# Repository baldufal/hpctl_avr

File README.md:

# HPCTL AVR
Software for Atmega48/88/168/328 controller of HPCTL heating and ventilation controller project.

We use it with Microchip Studio and Atmega168.

# Task
This mc is controlled by a [ESP32](https://github.com/baldufal/hpctl_arduino/tree/main) via I2C bus.
It drives 8 solid state relais (SSRs) and 8 mechanical relais and reports the state of 4 universal binary inputs.
3 of the SSRs are connected to a heater. They are driven with very slow PWM with a period of 10s.
The mechanical relais control one ventilator.
Another ventilator is controlled via PWM on one of the SSR outputs (SSR3/PD3).

# I2C Interface
The I2C interface exposes 6 8bit registers:
Register | Semantics | Allowed values (writing)
---|---|---
0 | Heater level | 0-30
1 | Vent IN | 0-255
2 | Vent OUT | 0-6
3 | SSRs | 0b000x0xxx
4 | Checksum | -
5 | Inputs | -

- The three most significant bits of register 3 are determined by heater level. They cannot be set manually, but their current values can be read from this register.
- Similarly for 4th bit (0b00001000) is controlled by the Vent OUT level (1kHz PWM).
- The checksum is the inverse of the 8bit sum of registers 0 to 3.
- The lower 4 bits of register 5 contain the actual input states.
- The upper 4 bits of register 5 contain the bitwise inverse of the input states.

# Board
We use the controller on a custom PCB. It additionally provides the corresponding ESP32 with 5V supply voltage and a debounced terminal for 4 buttons which are connected directly to the ESP32.

The layout file uses a wrong footprint for the mC.

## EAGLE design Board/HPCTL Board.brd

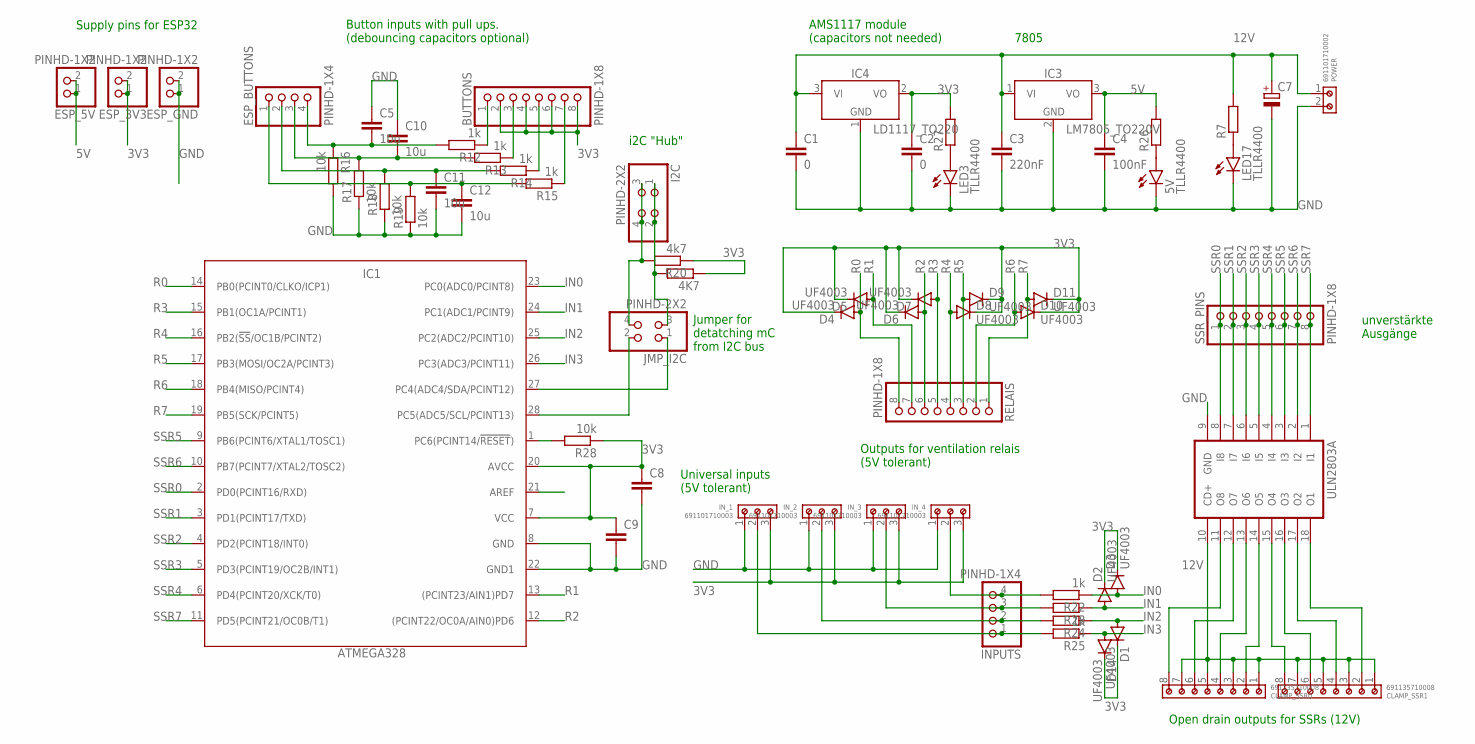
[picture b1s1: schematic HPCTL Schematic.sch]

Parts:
4K7: R-EU_0207/10; 0207/10
5V: TLLR4400; LED3MM
BUTTONS: PINHD-1X8; 1X08
C1, C2: 0; C0805K
C3: 220nF; C0805K
C4: 100nF; C0805K
C5, C10, C11, C12: 10u; C0805K
C7: CPOL-EUE2-5; E2-5
C8, C9: C-EUC0805K; C0805K
CLAMP_SSR0, CLAMP_SSR1: 691135710008
D1, D2, D3, D4, D5, D6, D7, D8, D9, D10, D11, D14: UF4003; DO41-10
ESP_3V3, ESP_5V: PINHD-1X2; 1X02
ESP_BUTTONS: PINHD-1X4; 1X04
ESP_GND: PINHD-1X2; 1X02
I2C: PINHD-2X2; 2X02
IC1: ATMEGA328; DIP1016W53P254L3467H457Q28B
IC3: LM7805_TO220V; TO220V
IC4: LD1117_TO220; TO220V
INPUTS: PINHD-1X4; 1X04
IN_1, IN_2, IN_3, IN_4: 691101710003
JMP_I2C: PINHD-2X2; 2X02
LED3, LED17: TLLR4400; LED3MM
POWER: 691101710002
R7, R23, R24, R26, R27: R-EU_0207/10; 0207/10
R12, R13, R14, R15, R22, R25: 1k; 0207/10
R16, R17, R18, R19, R28: 10k; 0207/10
R20: 4k7; 0207/10
RELAIS: PINHD-1X8; 1X08
SSR_PINS: PINHD-1X8; 1X08
ULN2803A: ULN2804A; DIL18

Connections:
3V3: 4K7.1, BUTTONS.2, BUTTONS.4, BUTTONS.6, BUTTONS.8, C2.1, C8.1, C9.1, D1.C, D2.C, D3.C, D4.C, D5.C, D6.C, D7.C, D8.C, D9.C, D10.C, D11.C, D14.C, ESP_3V3.1, ESP_3V3.2, IC1.7 (VCC), IC1.20 (AVCC), IC4.2 (VO), IN_1.3, IN_2.3, IN_3.3, IN_4.3, R20.1, R27.2, R28.1
5V: C4.1, ESP_5V.1, ESP_5V.2, IC3.3 (VO), R26.2
12V: C1.1, C3.1, C7.+, CLAMP_SSR0.1, CLAMP_SSR0.3, CLAMP_SSR0.5, CLAMP_SSR0.7, CLAMP_SSR1.1, CLAMP_SSR1.3, CLAMP_SSR1.5, CLAMP_SSR1.7, IC3.1 (VI), IC4.3 (VI), POWER.1, R7.2, ULN2803A.10 (CD+)
GND: 5V.K (C), C1.2, C2.2, C3.2, C4.2, C5.1, C7.-, C8.2, C9.2, C10.1, C11.2, C12.2, ESP_GND.1, ESP_GND.2, IC1.8 (GND), IC1.22 (GND1), IC3.2 (GND), IC4.1 (GND), IN_1.1, IN_2.1, IN_3.1, IN_4.1, LED3.K (C), LED17.K (C), POWER.2, R16.2, R17.1, R18.1, R19.1, ULN2803A.9 (GND)
IN0: D3.A, IC1.23 (PC0(ADC0/PCINT8)), R22.1
IN1: D2.A, IC1.24 (PC1(ADC1/PCINT9)), R23.1
IN2: D1.A, IC1.25 (PC2(ADC2/PCINT10)), R24.1
IN3: D14.A, IC1.26 (PC3(ADC3/PCINT11)), R25.1
unnamed: I2C.3, I2C.4, JMP_I2C.4, R20.2
unnamed: 4K7.2, I2C.1, I2C.2, JMP_I2C.3
unnamed: BUTTONS.7, R15.1
unnamed: BUTTONS.5, R14.1
unnamed: BUTTONS.3, R13.1
unnamed: BUTTONS.1, R12.1
unnamed: LED17.A, R7.1
unnamed: CLAMP_SSR0.8, ULN2803A.11 (O8)
unnamed: CLAMP_SSR0.6, ULN2803A.12 (O7)
unnamed: CLAMP_SSR0.4, ULN2803A.13 (O6)
unnamed: CLAMP_SSR0.2, ULN2803A.14 (O5)
unnamed: CLAMP_SSR1.8, ULN2803A.15 (O4)
unnamed: CLAMP_SSR1.6, ULN2803A.16 (O3)
unnamed: CLAMP_SSR1.4, ULN2803A.17 (O2)
unnamed: CLAMP_SSR1.2, ULN2803A.18 (O1)
unnamed: C5.2, ESP_BUTTONS.4, R12.2, R16.1
unnamed: C12.1, ESP_BUTTONS.1, R15.2, R19.2
unnamed: C11.1, ESP_BUTTONS.2, R14.2, R18.2
unnamed: INPUTS.4, IN_4.2, R22.2
unnamed: C10.2, ESP_BUTTONS.3, R13.2, R17.2
unnamed: INPUTS.3, IN_3.2, R23.2
unnamed: INPUTS.2, IN_2.2, R24.2
unnamed: INPUTS.1, IN_1.2, R25.2
unnamed: 5V.A, R26.1
unnamed: LED3.A, R27.1
unnamed: IC1.1 (PC6(PCINT14/!RESET!)), R28.2
R0: D4.A, IC1.14 (PB0(PCINT0/CLKO/ICP1)), RELAIS.8
R1: D5.A, IC1.13 ((PCINT23/AIN1)PD7), RELAIS.7
R2: D6.A, IC1.12 ((PCINT22/OC0A/AIN0)PD6), RELAIS.6
R3: D7.A, IC1.15 (PB1(OC1A/PCINT1)), RELAIS.5
R4: D8.A, IC1.16 (PB2(!SS!/OC1B/PCINT2)), RELAIS.4
R5: D9.A, IC1.17 (PB3(MOSI/OC2A/PCINT3)), RELAIS.3
R6: D10.A, IC1.18 (PB4(MISO/PCINT4)), RELAIS.2
R7: D11.A, IC1.19 (PB5(SCK/PCINT5)), RELAIS.1
SCL: IC1.28 (PC5(ADC5/SCL/PCINT13)), JMP_I2C.2
SDA: IC1.27 (PC4(ADC4/SDA/PCINT12)), JMP_I2C.1
SSR0: IC1.2 (PD0(PCINT16/RXD)), SSR_PINS.1, ULN2803A.8 (I8)
SSR1: IC1.3 (PD1(PCINT17/TXD)), SSR_PINS.2, ULN2803A.7 (I7)
SSR2: IC1.4 (PD2(PCINT18/INT0)), SSR_PINS.3, ULN2803A.6 (I6)
SSR3: IC1.5 (PD3(PCINT19/OC2B/INT1)), SSR_PINS.4, ULN2803A.5 (I5)
SSR4: IC1.6 (PD4(PCINT20/XCK/T0)), SSR_PINS.5, ULN2803A.4 (I4)
SSR5: IC1.9 (PB6(PCINT6/XTAL1/TOSC1)), SSR_PINS.6, ULN2803A.3 (I3)
SSR6: IC1.10 (PB7(PCINT7/XTAL2/TOSC2)), SSR_PINS.7, ULN2803A.2 (I2)
SSR7: IC1.11 (PD5(PCINT21/OC0B/T1)), SSR_PINS.8, ULN2803A.1 (I1)

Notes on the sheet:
Button inputs with pull ups. (debouncing capacitors optional)
7805
AMS1117 module (capacitors not needed)
Supply pins for ESP32
Jumper for detatching mC from I2C bus
i2C "Hub"
unverstärkte Ausgänge
Open drain outputs for SSRs (12V)
Outputs for ventilation relais (5V tolerant)
Universal inputs (5V tolerant)

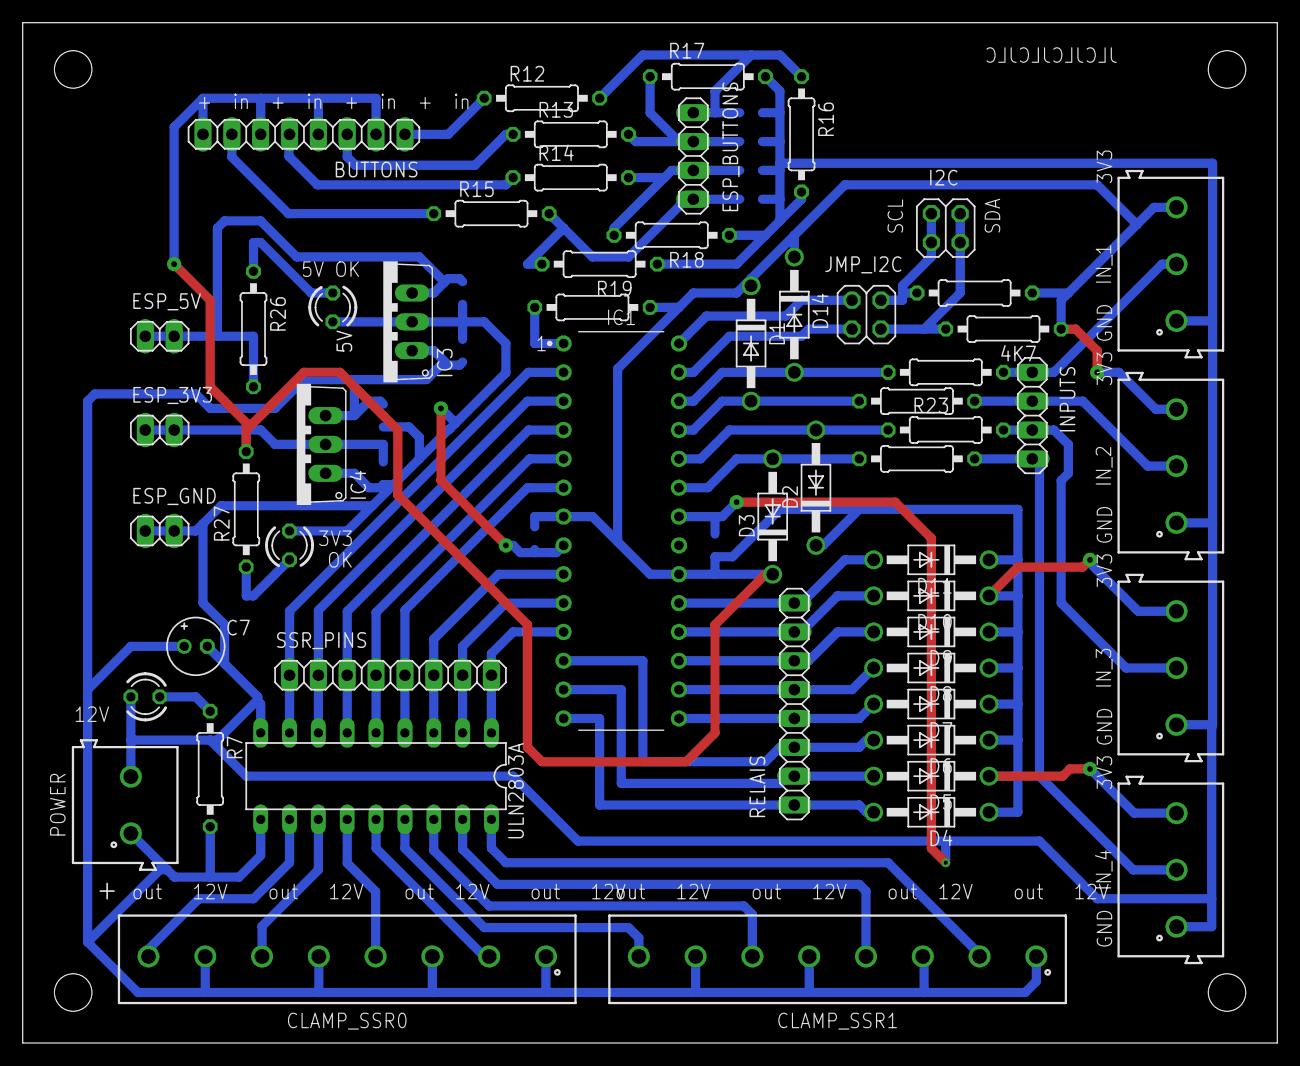
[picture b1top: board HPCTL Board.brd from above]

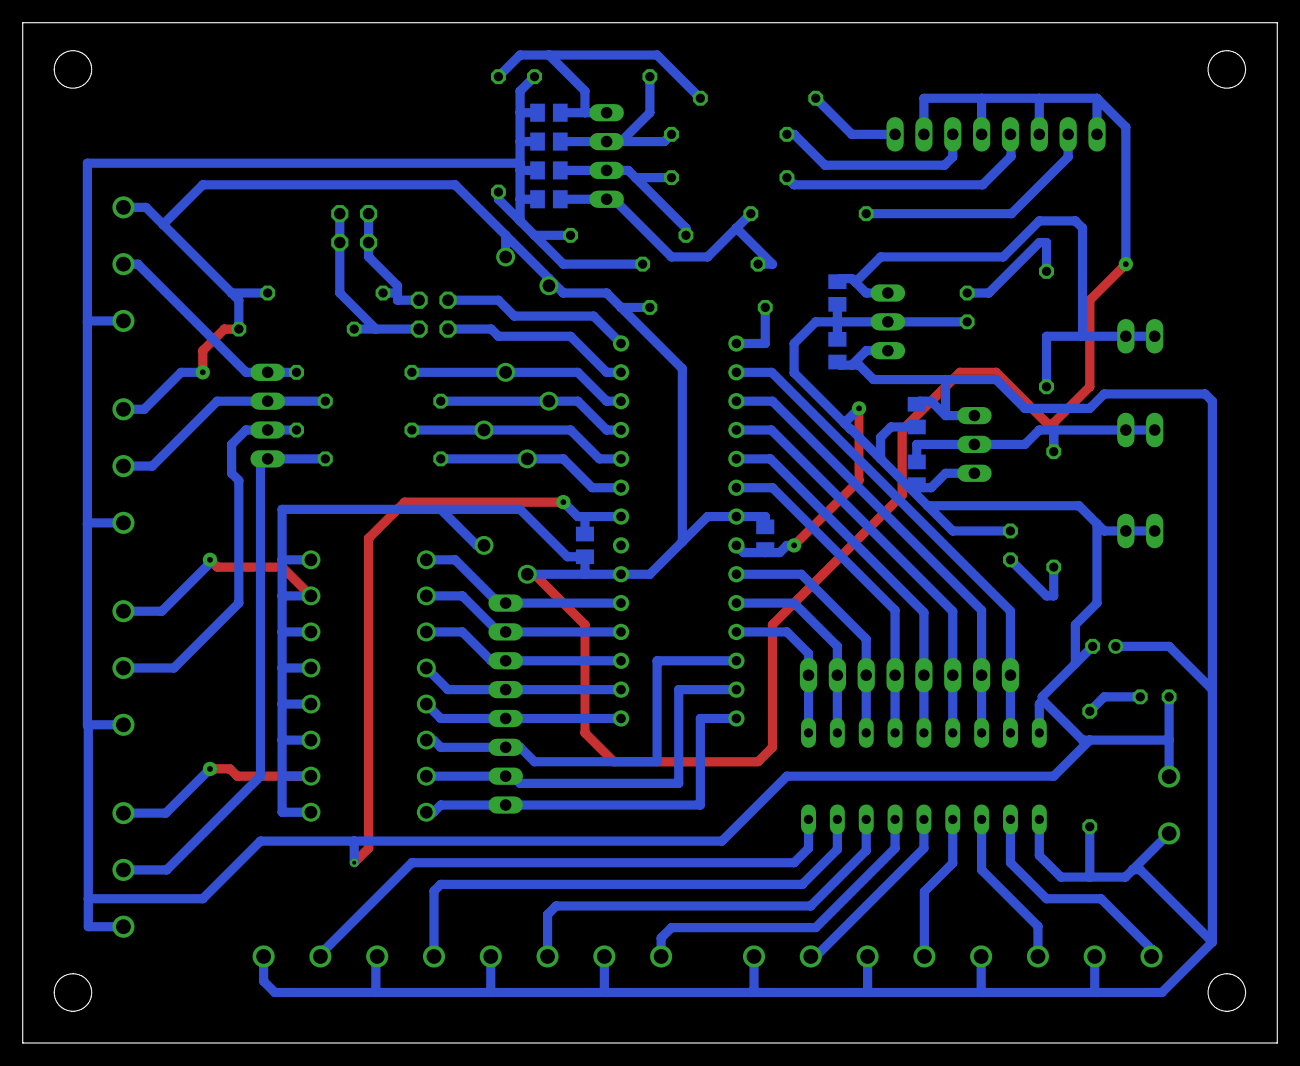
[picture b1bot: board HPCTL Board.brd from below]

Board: 2 copper layers, 110.5 x 89.8 mm, 65 parts (10 on the bottom side), 52 nets.

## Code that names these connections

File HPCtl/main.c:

/*
* HPCtl.c
*
* Created: 05.10.2023 19:40:37
* For Atmega168
* Author : falkb
*/

#ifndef F_CPU
# define F_CPU 8000000UL
#endif

#include <avr/io.h>
#include <avr/interrupt.h>
#include <avr/wdt.h>
#include <util/delay.h>
#include "twislave.h"
#include "relay.h"

#define PWM_TICK_FREQUENCY_HZ 1
#define PWM_PERIOD_SECONDS 10
// The number of heater levels, defined by the PWM cycle.
#define NUM_HEATER_LEVELS (PWM_TICK_FREQUENCY_HZ * PWM_PERIOD_SECONDS * 3 + 1)

// A tick-counter driven by a timer.
// This counts seconds modulo some number.
volatile uint8_t timer_ticks;

// Initializes outputs.
static void io_init() {
	// No pull ups necessary because of external pull ups.
	// We use pull ups anyway to make debugging without external pull ups easier.
	
	// Outputs:
	// PD0..PD2, PD4:		General purpose SSRs
	// PD3:					Ventilation PWM
	// PD5, PB6, PB7:		Heater SSRs
	// PD6, PD7, PB0..PB5:	Relais
	
	// Inputs:
	// PC0..PC3:			General purpose Inputs
	// PC4, PC5:			I2C
	
	// Vent pins high = vent off
	PORTB = 0b00111111;
	DDRB = 0xFF;
	
	// PC0 to PC5 as inputs with pull ups enabled
	PORTC = 0xFF;
	DDRC = 0x00;
	
	// Vent pins high = vent off
	PORTD = 0b11000000;
	DDRD = 0xFF;
	
}

static void init_heater_timer() {
	// See http://www.8bit-era.cz/arduino-timer-interrupts-calculator.html
	// Or https://www.arduinoslovakia.eu/application/timer-calculator

	// ! Make sure this fits with PWM_TICK_FREQUENCY_HZ !

	TCCR1A = 0; // set entire TCCR1A register to 0
	TCCR1B = 0; // same for TCCR1B
	TCNT1 = 0; // initialize counter value to 0
	// set compare match register for 1 Hz increments
	OCR1A = 31249; // = 8000000 / (256 * 1) - 1 (must be <65536)
	// turn on CTC mode
	TCCR1B |= (1 << WGM12);
	// Set CS12, CS11 and CS10 bits for 256 prescaler
	TCCR1B |= (1 << CS12);
	// enable timer compare interrupt
	TIMSK1 |= (1 << OCIE1A); // Atmega8: TIMSK |= (1 << OCIE1A);
}

void init_vent_pwm_timer() {
	// Set initial duty cycle to 0/255
	OCR2B = 0;
	
	// Fast PWM Mode (WGM22:0 = 3), non-inverting mode on OC2B
	TCCR2A = (1 << COM2B1) | (1 << WGM21) | (1 << WGM20);
	
	// f_pwm = f_clk / (Prescaler * 256)
	// Prescaler = 32 => 980Hz
	TCCR2B = (1 << CS21) | (1 << CS20);
}


// Reads input pins PC0..PC3
static void readout() {
	// Read PC0..PC3
	uint8_t values = PINC & 0x0F;
	
	// Compute shifted complement
	uint8_t complement = ~values;
	complement = complement << 4;

	// Write to I2C buffer
	i2cdata[5] = complement | values;
}

static void compute_checksum(){
	cli();
	
	uint8_t sum = 0;
	sum += i2cdata[0];
	sum += i2cdata[1];
	sum += i2cdata[2];
	sum += i2cdata[3];
	i2cdata[4] = ~sum;
	
	sei();
}

static void set_heater(uint8_t level, uint8_t pwm_counter){
	if (level > 20) {
		PORTB |= (1<<PORTB6);
		PORTB |= (1<<PORTB7);
		uint8_t remainder = level - 20;
		if (remainder > pwm_counter) {
			PORTD |= (1<<PORTD5);
			} else {
			PORTD &= ~(1<<PORTD5);
		}
	}
	else {
		if (level > 10) {
			PORTB |= (1<<PORTB6);
			PORTD &= ~(1<<PORTD5);
			uint8_t remainder = level - 10;
			if (remainder > pwm_counter) {
				PORTB |= (1<<PORTB7);
				} else {
				PORTB &= ~(1<<PORTB7);
			}
		}
		else {
			PORTD &= ~(1<<PORTD5);
			PORTB &= ~(1<<PORTB7);
			if (level > pwm_counter) {
				PORTB |= (1<<PORTB6);
				} else {
				PORTB &= ~(1<<PORTB6);
			}
		}
	}

	// Expose SSR state to i2c.
	cli();
	i2cdata[3] &= 0b00011111;
	if(PORTB & (1<<PORTB6))
	i2cdata[3] |= (1<<5);
	if(PORTB & (1<<PORTB7))
	i2cdata[3] |= (1<<6);
	if(PORTD & (1<<PORTD5))
	i2cdata[3] |= (1<<7);
	sei();
}

static void set_ssrs(uint8_t value){
	// Mask out unaffected bits.
	uint8_t mask_reg_d = 0b00011111;
	value &= mask_reg_d;
	
	PORTD = (PORTD & ~mask_reg_d) | value;
}

static void set_air_out(uint8_t	value){
	OCR2B = value;
}

ISR(TIMER1_COMPA_vect) // every 1s
{
	timer_ticks = (timer_ticks + 1) % (PWM_PERIOD_SECONDS * PWM_TICK_FREQUENCY_HZ);
}


int main(void)
{
	io_init();
	// Enable watchdog to restart if we didn't reset it for 2 seconds.
	wdt_enable(WDTO_2S);
	// Enable I2C.
	init_twi_slave(I2C_SLAVE_ADDRESS);
	// Read input values
	readout();
	// Init 1Hz timer for the 3 heater SSRs
	init_heater_timer();
	// Init timer2 for ventilation PWM
	init_vent_pwm_timer();
	// Enable Interrupts.
	sei();
	
	while (1)
	{
		// Reset watchdog timer.
		wdt_reset();
		
		readout();
		
		compute_checksum();
		
		set_heater(i2cdata[0], timer_ticks);
		
		set_air_in(i2cdata[1]);
		set_air_out(i2cdata[2]);
		
		set_ssrs(i2cdata[3]);
	}
}

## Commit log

2023-11-01 Add project
2023-11-02 Add board files
2025-04-18 Change vent_in to PWM
2025-04-18 Update README.md
    Adapt to PWM control of Vent IN

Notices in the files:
parts and their libraries:
Wurth_Connectors_WR-TBL Wire Protector: Copyright: Würth Elektronik
